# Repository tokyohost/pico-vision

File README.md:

# Pico RP2040 系统监控屏

项目包含电脑端数据采集程序和 Pico RP2040 显示程序，实现两个独立功能：

1. 按开发板型号非阻塞控制 WS2812 多色灯或 GPIO 单色状态灯。
2. 通过 USB CDC 或 Wi-Fi WebSocket 增量接收 JSON，并将 ST7789 LCD 按条带异步刷新。

## 设计约束

- 不使用 RP2040 第二核心，规避 MicroPython 线程、USB 和 SPI 之间的互锁风险。
- 内置 USB CDC 仅用于 REPL；PV1 通信使用独立 USB CDC 及非阻塞批量 FIFO。
- LCD 不申请 240×320 的整帧缓冲，仅使用 240×48×2，即 23,040 字节条带缓冲。
- LED、串口接收和 LCD 刷新均由单核协作式主循环调度。
- JSON 最大长度为 16 KiB，超限数据包会被拒绝。

## Pico 端文件

将 `picoRP2040/` 的完整目录结构复制到 Pico 根目录：

- `main.py`：应用入口和协作式主循环。
- `led/`：不同板载状态灯的非阻塞控制策略与控制器工厂。
- `protocol.py`：PV1 握手及 JSON 增量接收状态机。
- `net/`：USB CDC、Wi-Fi、WebSocket 传输策略及首连接锁定选择器。
- `usb_transport.py`：创建与 REPL 隔离的 USB CDC 数据通道。
- `usb/device/`：上游 MicroPython `usb-device` 和 `usb-device-cdc` MIT 实现。
- `upgrade_manager.py`：串口升级会话、临时写入、SHA-256 校验、安装和自动重启。
- `data_receiver.py`：最新 JSON 快照缓存。
- `lcd.py`：ST7789 初始化和区域写屏。
- `canvas.py`：带条带裁剪的 RGB565 绘图。
- `dashboard.py`：仪表盘布局和分段刷新。
- `config.py`：开发板、屏幕方案、周期和协议配置。
- `color_manager.py`：按屏幕型号管理反色模式和 RGB/BGR 颜色顺序。
- `board_manager.py`：注册开发板硬件档案并隔离不同板载 LED 类型。
- `fonts/`：SDK 内置文泉驿点阵正黑和 Fusion Pixel 双语字模的授权说明。

Pico 握手会向 Monitor 返回当前开发板型号、屏幕色彩方案、运行固件版本和 `net` 状态；ESP32-S3 还会返回由 eFuse MAC 经 SHA-256 派生的稳定 `device_id`，设备管理页面以 UUID 形式展示且不暴露原始 MAC。USB 模式返回 `mode=usb`，Wi-Fi 模式还返回 SSID、IP、网关、RSSI、WebSocket 端口与路径。源码
直接部署时版本为 `development`，发布全量固件包会自动写入对应的发布版本。

开发板型号和 Wi-Fi 开关由 `picoRP2040/config.py` 配置。例如 ESP32-S3 开启 Wi-Fi：

```python
BOARD_MODEL = "ESP32-S3"
WIFI_ENABLED = True
```

ESP32-S3 与 RP2040 都遵循样式声明的默认字体，例如现有紧凑样式使用
`font_name = "screen_2inch_compact"`。需要显示中文时，可通过 `canvas.text()` 的
`font_name` 参数为单次文字绘制选择字体；调用结束后会恢复样式默认字体。

项目配套的 RP2040 与 ESP32-S3 固件还可选择 `wqy_8x16` 或
`fusion_pixel_8x16`。两者均为英文半角 8×16、中文全角 16×16，直接由 `fn_canvas`
从固件只读区绘制。`canvas.text()` 和 `canvas.text_width()` 都接受 `font_name`；不传入
时保持当前样式字体，样式未指定时仍默认 `native`。

仅使用 USB CDC 时把 `WIFI_ENABLED` 设为 `False`，固件不会初始化无线网卡或 WebSocket 服务。支持的板型包括：

- `rp2040_usb`：GP22 上的 WS2812 多色状态灯。
- `rp2040_typec`：GP25 控制的单色状态灯。
- `ESP32-S3`：默认使用 GPIO48 上的板载 WS2812；具体开发板引脚不同时可修改 `board_manager.py` 中的档案。

新增型号时，可创建 `BoardProfile` 并通过 `register_board_profile()` 注册；业务层
无需感知 LED 的具体实现。

USB 能力同样按照 `BOARD_MODEL` 自动选择，不需要额外 USB 开关：

- `rp2040_usb`、`rp2040_typec` 使用 `machine.USBDevice` 注册保留 REPL 的独立数据 CDC。
- `ESP32-S3` 使用固件内置 USB CDC 或 USB 串行控制台，通过 `sys.stdin` 与
  `sys.stdout` 承载 PV1，不导入也不调用 ESP32 不支持的 `machine.USBDevice`。

ESP32-S3 内置控制台在收到 Monitor 首个字节后锁定 USB 会话；长期无通信后释放，
使启用 Wi-Fi 时 WebSocket 仍可参与传输竞选。

RP2040 端需要 MicroPython 1.23 或更新版本。启动后 USB 会重新枚举为
两个串口：一个保留给 REPL，另一个由 Monitor 通过 PV1 PING 自动识别。
首次部署后原串口短暂断开属于正常现象。Debian 下建议将
`PICO_MONITOR_PORT` 留空，不要固定 `/dev/ttyACM0`。

屏幕硬件由 `picoRP2040/config.py` 中的 `LCD_DEVICE_TYPE` 选择。编码由
芯片、尺寸、排针数量和批次组成，最终由 `lcd` 目录中对应的 `LcdDevice` 子类完整
定义脚位、分辨率、色彩、偏移和写屏细节。工厂会自动扫描该目录中公开
`LCD_DEVICE_CLASS` 的模块，无需维护集中式型号表：

- `st7789-2inch-8pin-a`：ST7789VW 二英寸八针 SPI A 款屏幕。
- `st7789-2.4inch-10pin-a`：ST7789 二点四英寸十针 SPI A 款屏幕。
- `st7789-2.4inch-8pin-b`：ST7789 二点四英寸八针 SPI B 款屏幕。

两种八针屏会按照 `BOARD_MODEL` 自动选择 GPIO。RP2040 保持原有
`SCK=GP6、MOSI=GP7、CS=GP8、DC=GP14、RST=GP15、BL=GP26`；ESP32-S3 使用
`SPI(2)、SCK=GPIO12、MOSI=GPIO11、CS=GPIO10、DC=GPIO9、RST=GPIO14、BL=GPIO13`。
ESP32-S3 默认以 10 MHz 驱动屏幕，并将不接屏幕的 MISO 显式分配到 GPIO15，避免
旧版 MicroPython 自动使用 GPIO13 而与背光 PWM 冲突。
完整接线见 `doc/ST7789_WIRING_README.md`。十针屏目前仅支持 RP2040，ESP32-S3
选择该方案时会返回明确错误，防止误用 RP2040 脚位。

屏幕色彩方案由所选屏幕档案确定，并在握手时提供给 Monitor：

- `st7789vw_2inch`：旧款 ST7789VW 二英寸屏，开启反色并使用 RGB 顺序。
- `st7789_2_4inch`：二点四英寸八针屏，关闭反色并使用 RGB 顺序。
- `st7789_2_4inch_10pin_a`：二点四英寸十针 A 款屏，开启反色并使用 RGB 顺序。
- `st7789_2_4inch_bgr`：新款屏的 BGR 变体；仅在红色与蓝色互换时使用。

旧配置名 `st7789_2inch` 仍可使用，并会自动映射到 `st7789vw_2inch`。

GitHub Actions 会按照全部开发板型号与规范 LCD 设备类型的笛卡尔积生成全量固件包，
文件名格式为 `OmniWatch-pico-full-v<版本>-<开发板型号>-<LCD设备类型>.zip`。包内直接保存
完整部署目录，不再包含 upgrade 清单。Windows Monitor 解压后通过 mpremote 比较设备端文件的
大小和 SHA-256，只复制缺失或内容不一致的文件。无型号后缀的兼容包固定对应
`rp2040_usb` 与 `st7789-2inch-8pin-a`，其他硬件不可混用该兼容包。

## 通信协议

PV1 帧可承载在 USB CDC 字节流或 WebSocket 二进制消息中。USB 和 WebSocket 同时可用时，设备始终优先锁定 USB。WebSocket 默认监听 `ws://设备IP:8765/pv1`，Monitor 握手会携带稳定客户端标识和本机设备名称；ESP32-S3 在 `websocket_clients.json` 中记录成功连接次数、最近地址、启用状态和优先级。设备管理页面可打开“WebSocket 客户端”查看、禁用或设置 `-1000` 至 `1000` 的优先级；仅严格更高优先级的新客户端能够抢占当前 WebSocket，会话切换时会清空旧缓冲，始终只允许一个客户端同步 JSON。

启用 JSON 发送间隔自适应后，Monitor 在每次建立发送会话时从 `400ms` 快速档开始协商；单次启动慢 ACK 不会立即降速，连续慢 ACK 才上调周期，ACK 超时则按两倍周期指数退避，恢复后立即采用更快周期。发送过程继续保持一条在途 JSON 的背压约束。最低采集与发送间隔为 `300ms`；固定间隔模式也不接受更低配置。

设备提供三个配网命令：`wifi.list` 每次返回按信号强度排序的附近全部网络，并在失败中的自动重连与扫描冲突时恢复无线状态后重试；`wifi.set` 的 `params` 接受 `ssid`、`password` 和可选 `timeout_ms`；`wifi.forget` 的 `params` 接受已保存的 `ssid`，用于删除设备凭据。命令均通过 `COMMAND` 帧返回成功详情或失败原因。Wi-Fi 凭据仅保存在设备端 `wifi_config.json`，PONG 和日志不会返回密码。

数据包采用纯 ASCII 行协议，避免 MicroPython 将二进制 `0x03` 解释为 Ctrl+C：

```text
JSON: + 单行 UTF-8 JSON + 换行符
```

设备发现命令为 `PING:PICO_LCD?\n`，有效 JSON 接收完成后返回 `ACK:JSON\n`。

## 启动方式

```powershell
python -m pip install -r requirements.txt
python send_frame.py
```

固定串口时可增加 `--port COM3` 参数。

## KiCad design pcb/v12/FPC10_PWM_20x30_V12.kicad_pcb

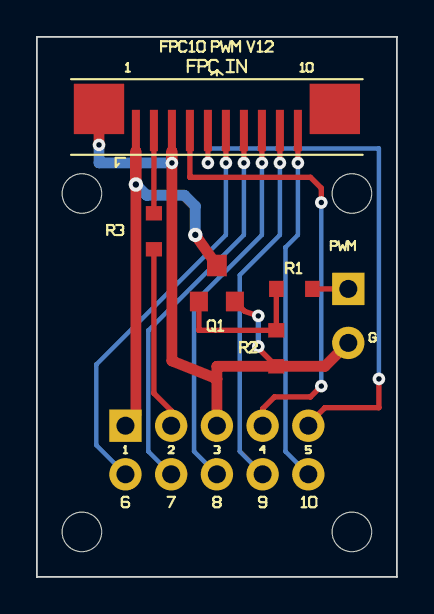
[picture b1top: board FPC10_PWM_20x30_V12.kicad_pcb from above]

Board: 2 copper layers, 20.0 x 30.0 mm, 11 parts (0 on the bottom side), 13 nets.

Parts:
H1: M2.2; H1
H2: M2.2; H2
H3: M2.2; H3
H4: M2.2; H4
J1: F-FPC1M10P-C310; J1
J2: 2x5 2.54mm Breakout; J2
J3: PWM/GND; J3
Q1: AO3400A; Q1
R1: 100R; R1
R2: 10K; R2
R3: 25R; R3

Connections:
CS: J1.6, J2.6
DC: J1.7, J2.7
GATE: Q1.1, R1.2, R2.1
GND: J1.3, J1.MP1, J2.3, J3.2, Q1.2, R2.2
LEDA: J2.2, R3.2
LEDA_FPC: J1.2, R3.1
LEDK: J1.1, J2.1, Q1.3
PWM: J3.1, R1.1
RST: J1.9, J2.9
SCL: J1.8, J2.8
SDA: J1.5, J2.5
SDO: J1.4, J2.4
VDD: J1.10, J2.10

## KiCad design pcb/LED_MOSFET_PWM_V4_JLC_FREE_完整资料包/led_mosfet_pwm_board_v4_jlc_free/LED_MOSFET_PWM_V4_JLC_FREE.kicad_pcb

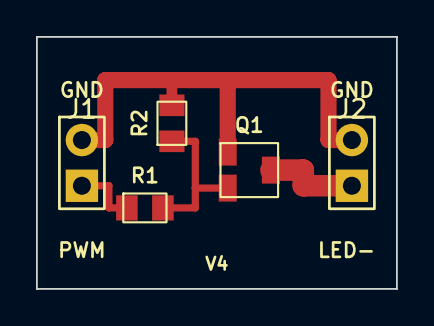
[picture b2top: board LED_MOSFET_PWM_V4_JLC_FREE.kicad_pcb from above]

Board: 2 copper layers, 20.0 x 14.0 mm, 5 parts (0 on the bottom side), 4 nets.

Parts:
J1: CTRL; PinHeader_1x02_P2.54mm_Vertical
J2: LOAD; PinHeader_1x02_P2.54mm_Vertical
Q1: AO3400A; SOT-23
R1: 100R; R_0805_2012Metric
R2: 10K; R_0805_2012Metric

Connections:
GATE: Q1.1, R1.2, R2.1
GND: J1.2, J2.2, Q1.2, R2.2
LED_MINUS: J2.1, Q1.3
PWM: J1.1, R1.1

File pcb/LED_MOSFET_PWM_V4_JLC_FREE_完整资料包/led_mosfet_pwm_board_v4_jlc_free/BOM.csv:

Comment,Designator,Footprint,Qty,Suggested Part
100R,R1,0805,1,0805 1% 100Ω
10K,R2,0805,1,0805 1% 10kΩ
AO3400A,Q1,SOT-23,1,"AO3400A, pin 1=G 2=S 3=D"
1x2 2.54mm,"J1,J2",PTH-2.54-1x2,2,Pin header or solder wires directly

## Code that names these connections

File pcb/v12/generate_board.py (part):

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# R2 is vertical and clearly separated from R1/Q1.
pads.append(Pad('R2','1',13.30,16.30,0.90,0.80,'rect','GATE','smd',0,('F.Cu',),True,True))
pads.append(Pad('R2','2',13.30,18.30,0.90,0.80,'rect','GND','smd',0,('F.Cu',),True,True))
# R3=25R directly in the FPC Pin-2 LEDA path, using the left-centre corridor.
pads.append(Pad('R3','1',6.50,9.80,0.90,0.80,'rect','LEDA_FPC','smd',0,('F.Cu',),True,True))
pads.append(Pad('R3','2',6.50,11.80,0.90,0.80,'rect','LEDA','smd',0,('F.Cu',),True,True))

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pads.append(Pad('VGMP1','',3.45,6.00,0.70,0.70,'circle','GND','via',0.30,('F.Cu','B.Cu'),False,False))
pads.append(Pad('VGMP2','',7.50,7.00,0.70,0.70,'circle','GND','via',0.30,('F.Cu','B.Cu'),False,False))
# V12 source crossover: GATE stays entirely on F.Cu; a short local GND
# bridge on B.Cu lets Q1 pin 2 reach R2/J3 ground without crossing GATE.
pads.append(Pad('VQ1S1','',12.30,15.50,0.70,0.70,'circle','GND','via',0.30,('F.Cu','B.Cu'),False,False))
pads.append(Pad('VQ1S2','',12.30,17.20,0.70,0.70,'circle','GND','via',0.30,('F.Cu','B.Cu'),False,False))
# FPC pins 6..10 fan out to ordered bottom-layer corridors.
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    w.writerow(['AO3400A','Q1','SOT-23','C20917','AO3400A',1,'SMT','Low-side LED- PWM MOSFET; FPC pin 1'])
    w.writerow(['100R','R1','0603','C22775','0603WAF1000T5E',1,'SMT','MOSFET gate series resistor'])
    w.writerow(['10K','R2','0603','C25804','0603WAF1002T5E',1,'SMT','Gate pulldown, default off'])
    w.writerow(['25R','R3','0603','DNP','Generic 25 ohm 0603',1,'Hand solder','Series resistor between FPC pin 2 and LEDA breakout; select 25 ohm'])
    w.writerow(['2x5 2.54mm header','J2','PinHeader_2x05_P2.54mm','DNP','Generic',1,'Hand solder','10-pin 1:1 breakout'])
    w.writerow(['1x2 2.54mm header','J3','PinHeader_1x02_P2.54mm','DNP','Generic',1,'Hand solder','PWM + GND input'])
with open(ORDER_DIR/'CPL_JLCPCB.csv','w',newline='',encoding='utf-8-sig') as f:
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with open(DOC_DIR/'PINOUT.csv','w',newline='',encoding='utf-8-sig') as f:
    w=csv.writer(f); w.writerow(['Pin','J1 FPC','J2 Breakout','Function / Note'])
    rows=[
        (1,'LEDK','LEDK','Backlight cathode / LED-; also connected to Q1 drain'),(2,'LEDA via R3=25R','LEDA','Backlight anode; FPC pin 2 is connected to J2 pin 2 through R3=25 ohm'),
        (3,'GND','GND','Logic/power ground; adjacent to LED- on the original board'),(4,'SDO','SDO','LCD serial data output / NC if unused'),
        (5,'SDA','SDA','SPI MOSI'),(6,'CS','CS','Chip select'),(7,'DC','DC','Data/command'),
        (8,'SCL','SCL','SPI clock'),(9,'RESET','RST','LCD reset'),(10,'VDD','VDD','LCD logic supply, nominal 3.3V'),
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
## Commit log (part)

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2026-06-30 init
2026-06-30 feat: 添加Pico LCD显示与帧接收功能
2026-06-30 feat: 替换Pico显示程序，新增JSON仪表盘渲染与系统状态采集
2026-06-30 feat: 重构Pico系统，分离LCD驱动、仪表盘渲染与主程序
2026-06-30 feat: 添加Pico WS2812控制示例，主循环实现RGB灯效切换
2026-06-30 feat: 重构Pico项目，迁移至picoRP2040目录，添加LED控制模块
2026-06-30 feat: 新增蓝灯数据提示功能，优化状态灯控制逻辑
